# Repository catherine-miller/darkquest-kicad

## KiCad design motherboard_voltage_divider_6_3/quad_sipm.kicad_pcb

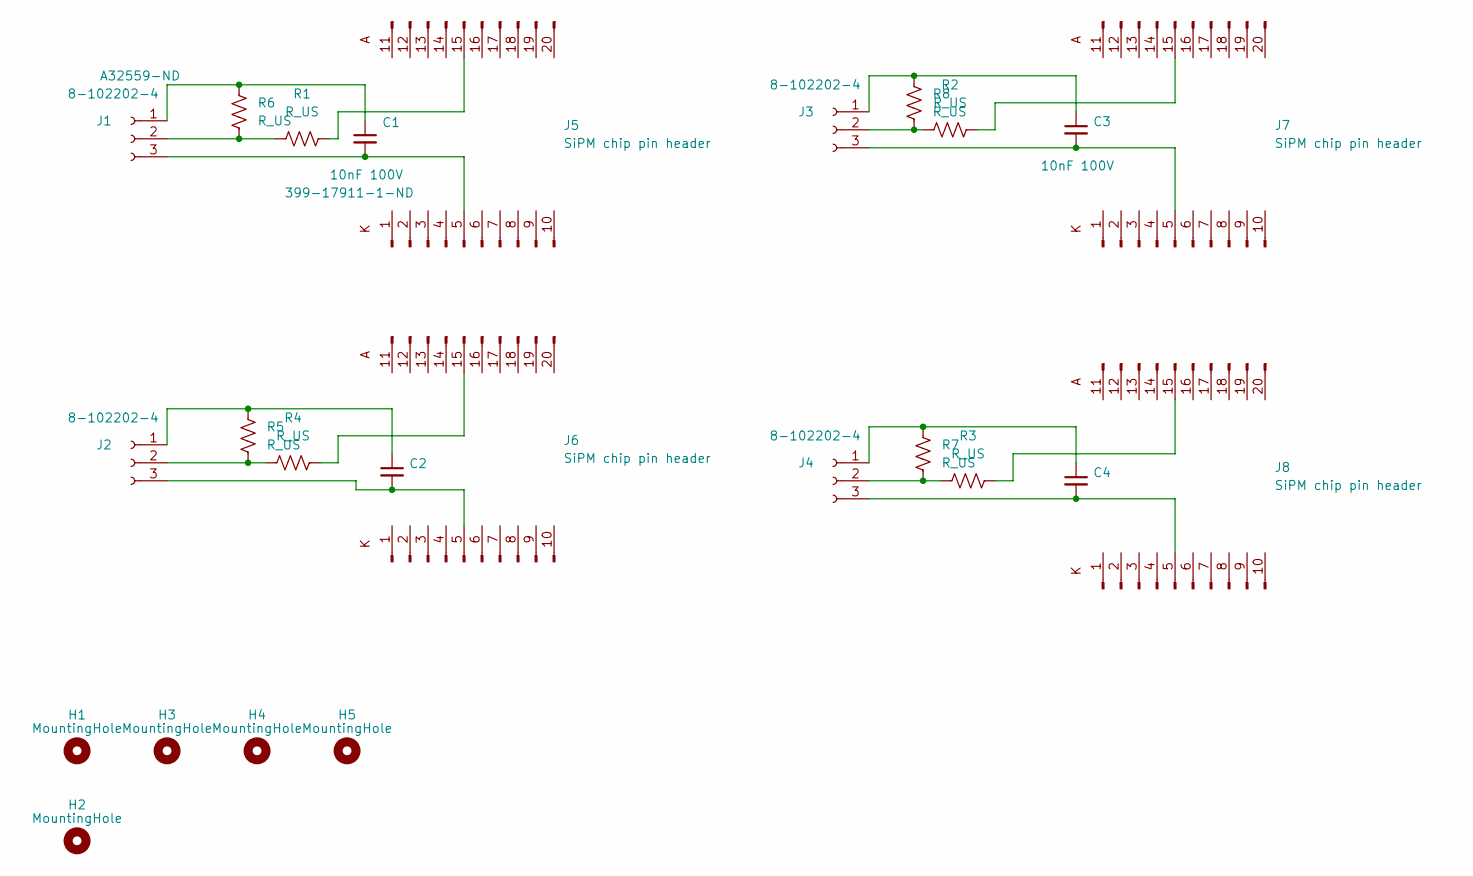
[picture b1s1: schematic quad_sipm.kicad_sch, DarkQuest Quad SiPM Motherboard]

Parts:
C1: 10nF 100V; 1206_VIS-L; DigiKey 399-17911-1-ND
C2, C3, C4: 10nF 100V; C_1206_3216Metric_Pad1.33x1.80mm_HandSolder; DigiKey 399-17911-1-ND
H1, H3, H4, H5: MountingHole; MountingHole_6.4_pad
H2: MountingHole; MountingHole_8.4mm_M8_Pad
J1, J2, J3, J4: 8-102202-4; PinHeader_1x03_P2.54mm_Vertical; DigiKey A32559-ND
J5, J6, J7, J8: SiPM chip pin header; chip_carrier_pin_header
R1, R2, R3, R4: R_US; 1206_VIS-L
R5, R6, R7, R8: R_US; 1206_VIS

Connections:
unnamed: C1.1, J1.1, R6.1
unnamed: J1.2, R1.1, R6.2
unnamed: C1.2, J1.3, J5.5
unnamed: C2.1, J2.1, R5.1
unnamed: J2.2, R4.1, R5.2
unnamed: C2.2, J2.3, J6.5
unnamed: C3.1, J3.1, R8.1
unnamed: J3.2, R2.1, R8.2
unnamed: C3.2, J3.3, J7.5
unnamed: C4.1, J4.1, R7.1
unnamed: J4.2, R3.1, R7.2
unnamed: C4.2, J4.3, J8.5
unnamed: J5.15 (Pin_5), R1.2
unnamed: J6.15 (Pin_5), R4.2
unnamed: J7.15 (Pin_5), R2.2
unnamed: J8.15 (Pin_5), R3.2

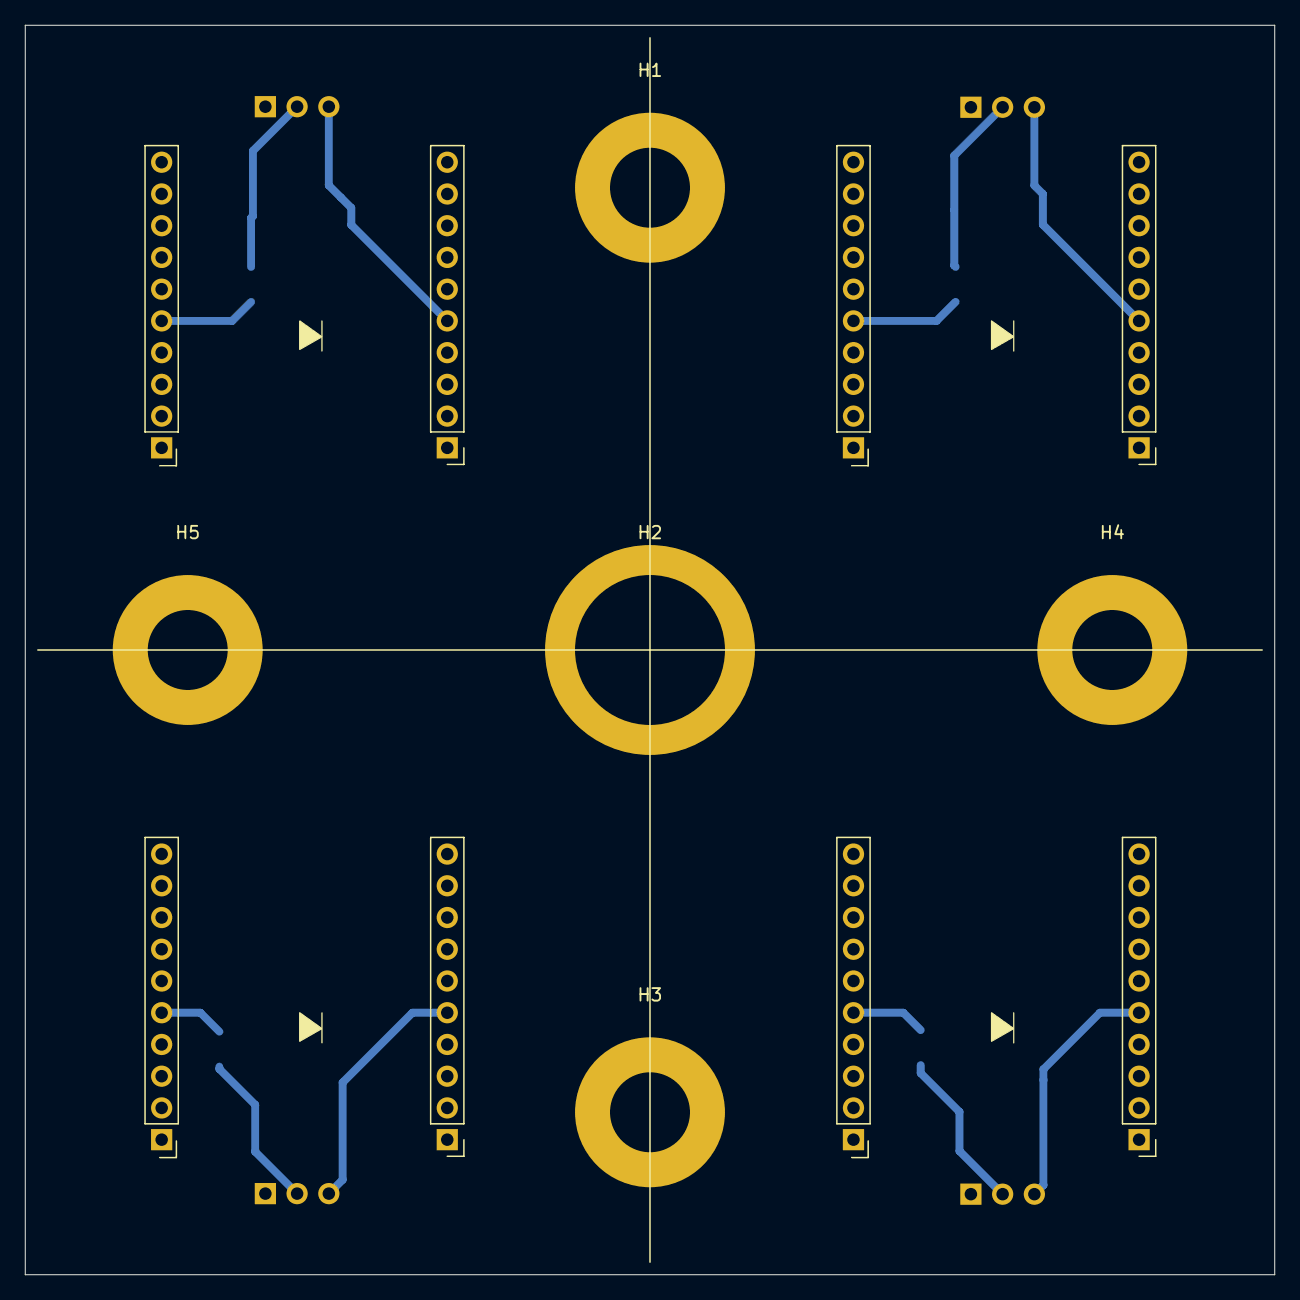
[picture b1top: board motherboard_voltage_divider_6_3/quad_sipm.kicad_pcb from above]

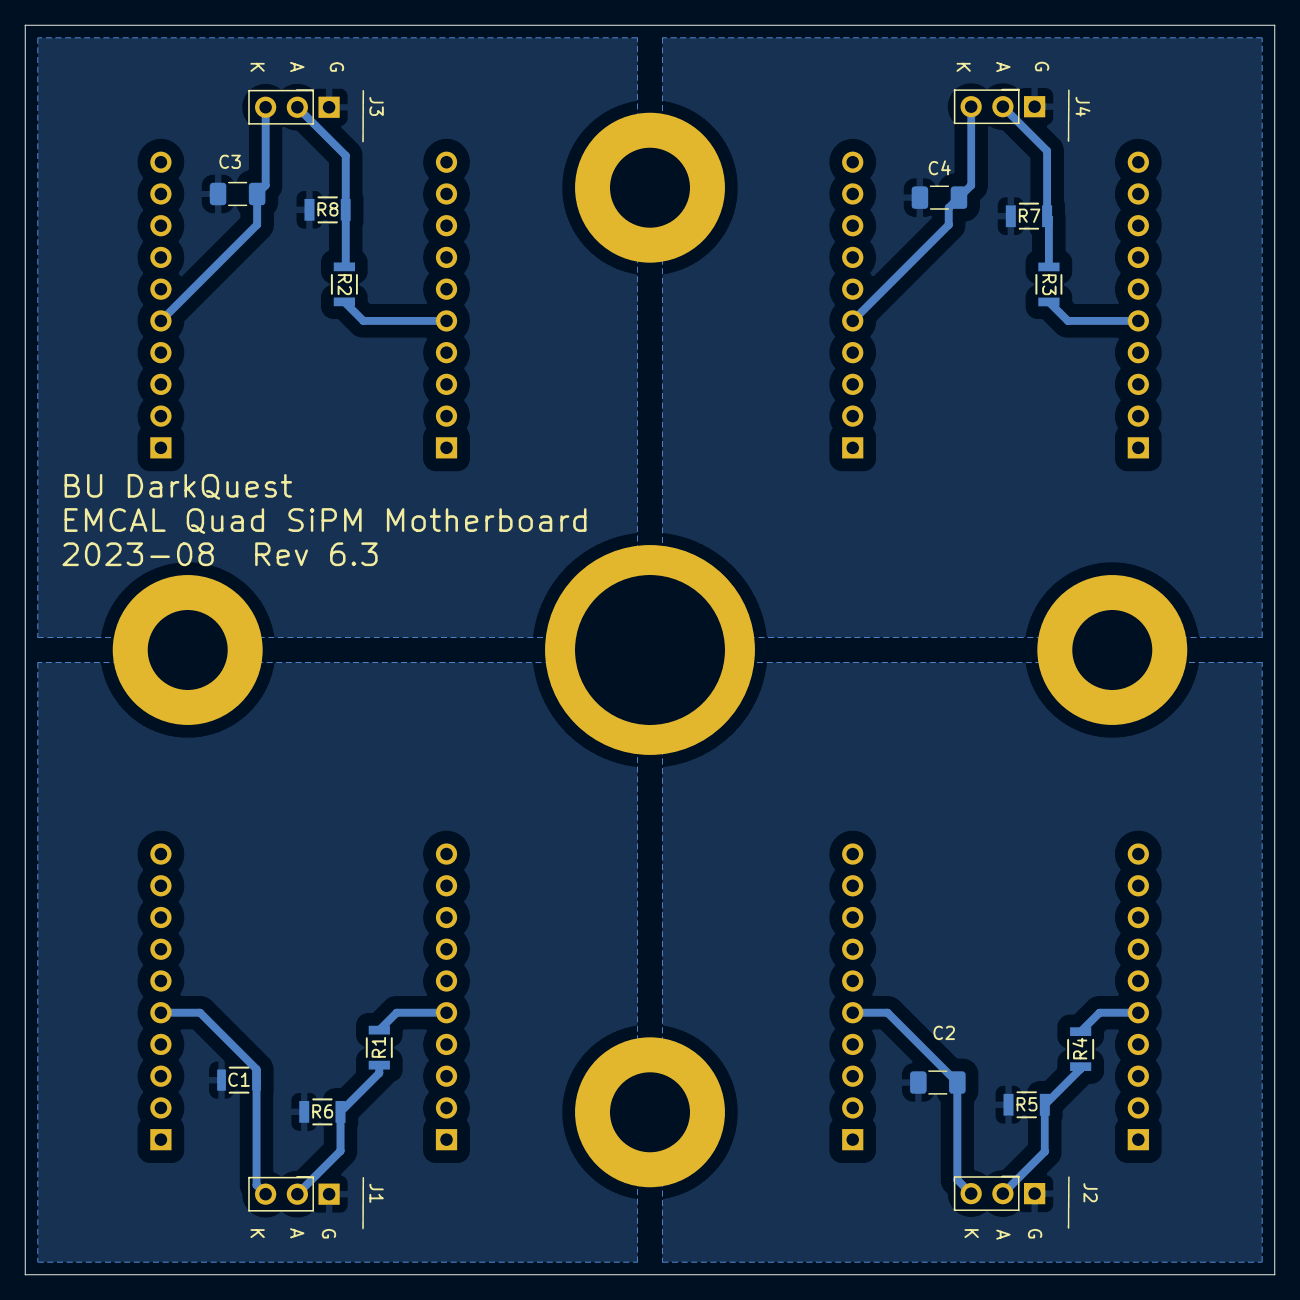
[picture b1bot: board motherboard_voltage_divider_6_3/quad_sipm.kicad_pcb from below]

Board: 2 copper layers, 100.0 x 100.0 mm, 25 parts (16 on the bottom side), 16 nets.

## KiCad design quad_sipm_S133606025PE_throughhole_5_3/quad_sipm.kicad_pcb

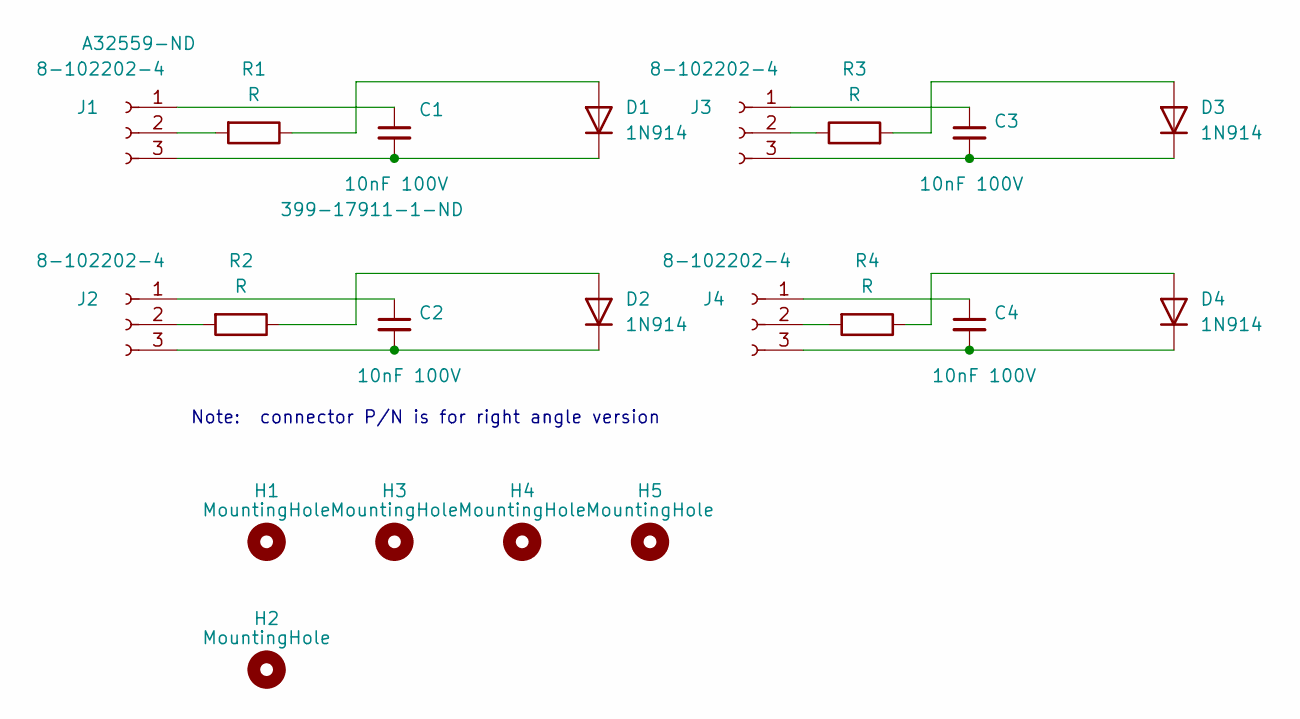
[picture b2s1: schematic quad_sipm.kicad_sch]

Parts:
C1, C2, C3, C4: 10nF 100V; C_1206_3216Metric_Pad1.33x1.80mm_HandSolder; DigiKey 399-17911-1-ND
D1, D2, D3, D4: 1N914; S13360-6025PE_throughhole
H1, H3, H4, H5: MountingHole; MountingHole_6.4_pad
H2: MountingHole; MountingHole_8.4mm_M8_Pad
J1, J2, J3, J4: 8-102202-4; PinHeader_1x03_P2.54mm_Vertical; DigiKey A32559-ND
R1, R2, R3, R4: R; 1206_VIS-L

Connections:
unnamed: D1.2 (A), R1.1
unnamed: C1.2, D1.1 (K), J1.3
unnamed: D2.2 (A), R2.1
unnamed: C2.2, D2.1 (K), J2.3
unnamed: D3.2 (A), R3.2
unnamed: C3.2, D3.1 (K), J3.3
unnamed: D4.2 (A), R4.1
unnamed: C4.2, D4.1 (K), J4.3
unnamed: C1.1, J1.1
unnamed: J1.2, R1.2
unnamed: C2.1, J2.1
unnamed: J2.2, R2.2
unnamed: C3.1, J3.1
unnamed: J3.2, R3.1
unnamed: C4.1, J4.1
unnamed: J4.2, R4.2

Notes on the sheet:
Note: connector P/N is for right angle version

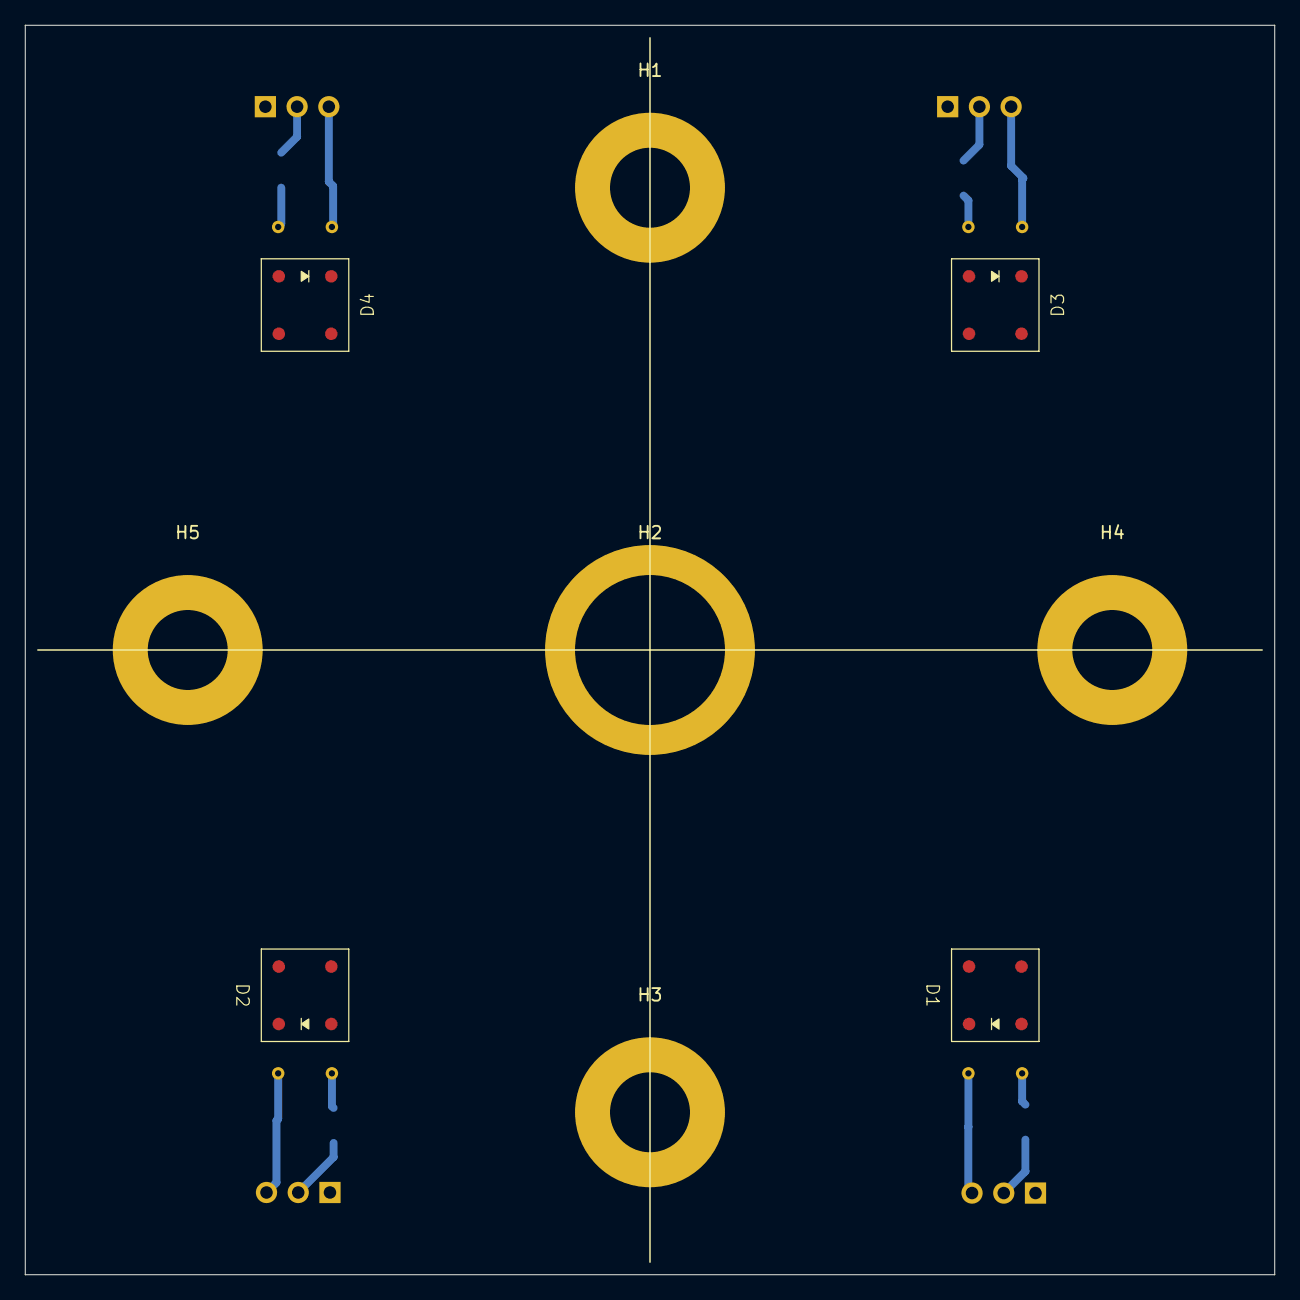
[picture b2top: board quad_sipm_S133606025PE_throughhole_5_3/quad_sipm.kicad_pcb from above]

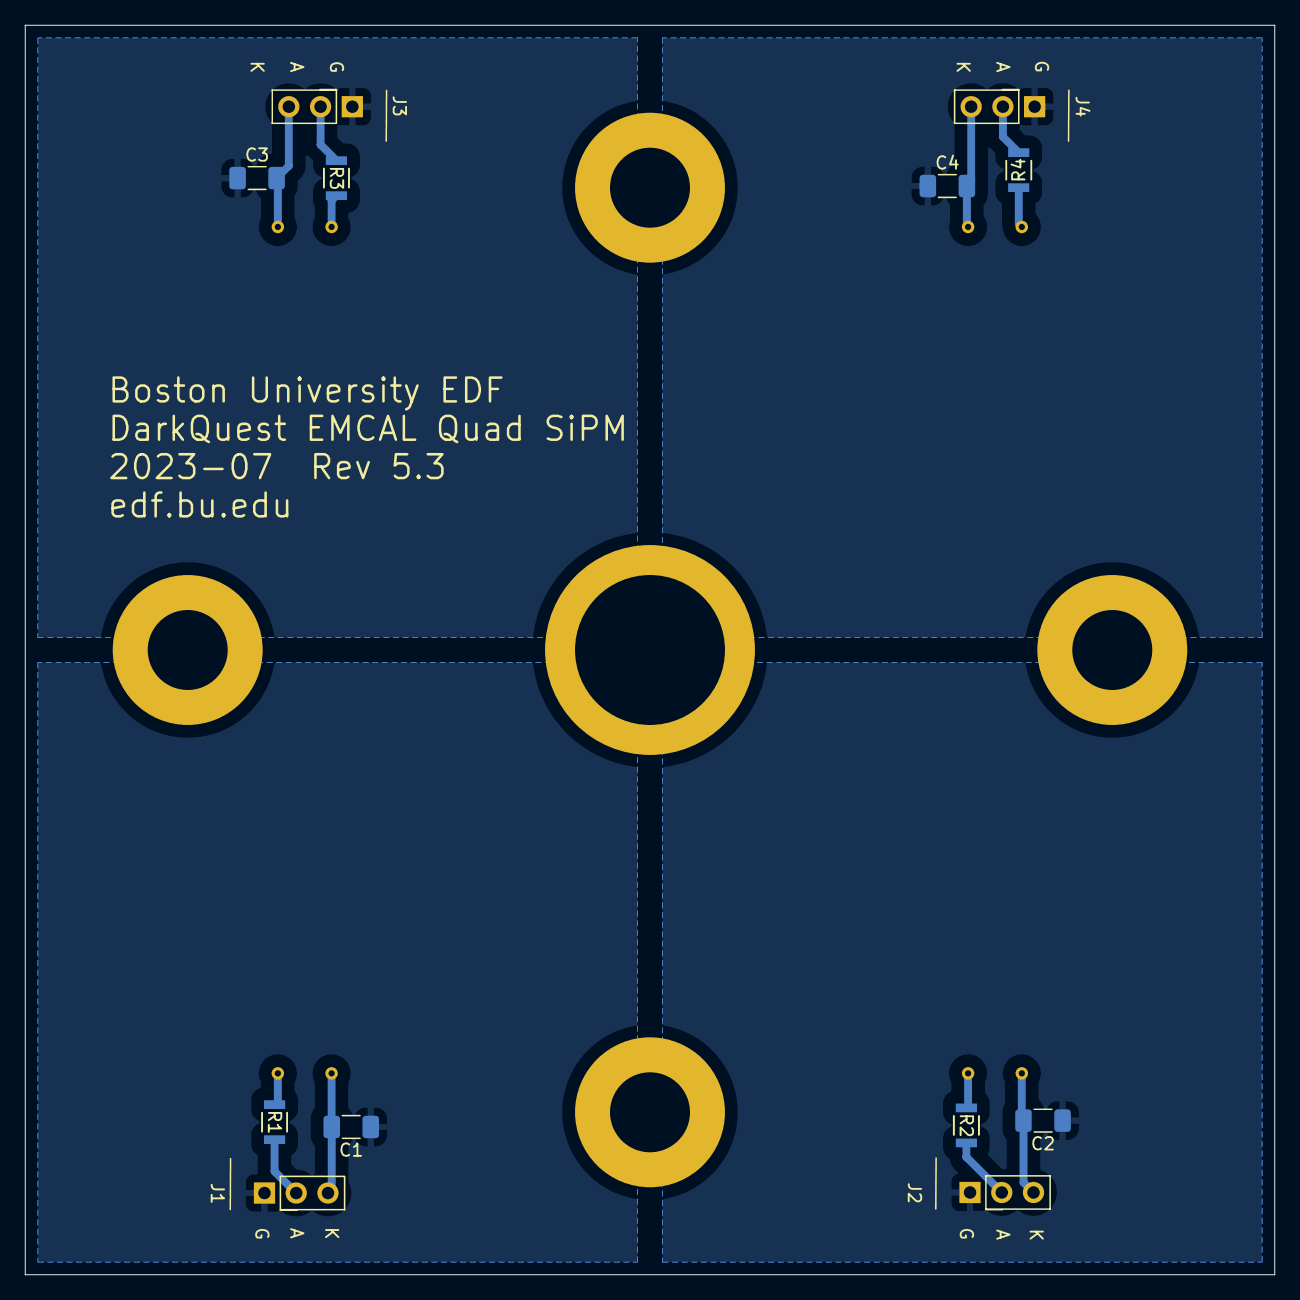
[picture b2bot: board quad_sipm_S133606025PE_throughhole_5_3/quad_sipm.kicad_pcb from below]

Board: 2 copper layers, 100.0 x 100.0 mm, 21 parts (12 on the bottom side), 16 nets.

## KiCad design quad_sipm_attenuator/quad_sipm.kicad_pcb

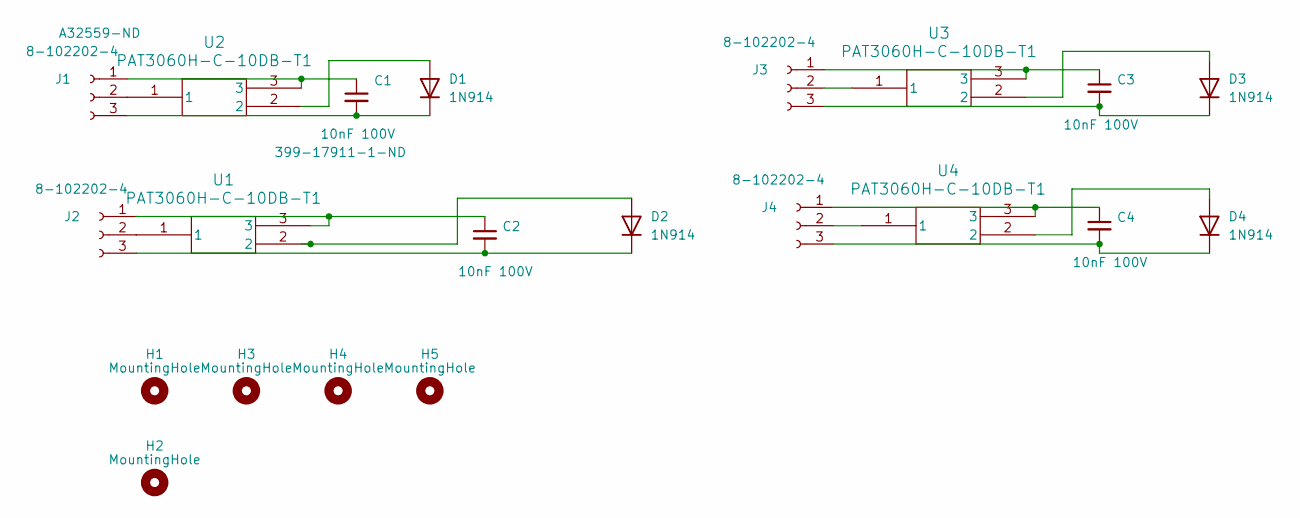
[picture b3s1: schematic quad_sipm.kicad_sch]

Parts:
C1, C2, C3, C4: 10nF 100V; C_1206_3216Metric_Pad1.33x1.80mm_HandSolder; DigiKey 399-17911-1-ND
D1, D2, D3, D4: 1N914; S13360-6025CS
H1, H3, H4, H5: MountingHole; MountingHole_6.4_pad
H2: MountingHole; MountingHole_8.4mm_M8_Pad
J1, J2, J3, J4: 8-102202-4; PinHeader_1x03_P2.54mm_Vertical; DigiKey A32559-ND
U1, U2, U3, U4: PAT3060H-C-10DB-T1; PAT3060H_SUS

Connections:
unnamed: D1.2 (A), U2.2
unnamed: C1.2, D1.1 (K), J1.3
unnamed: D2.2 (A), U1.2
unnamed: C2.2, D2.1 (K), J2.3
unnamed: D3.2 (A), U3.2
unnamed: C3.2, D3.1 (K), J3.3
unnamed: D4.2 (A), U4.2
unnamed: C4.2, D4.1 (K), J4.3
unnamed: C1.1, J1.1, U2.3
unnamed: J1.2, U2.1
unnamed: C2.1, J2.1, U1.3
unnamed: J2.2, U1.1
unnamed: C3.1, J3.1, U3.3
unnamed: J3.2, U3.1
unnamed: C4.1, J4.1, U4.3
unnamed: J4.2, U4.1

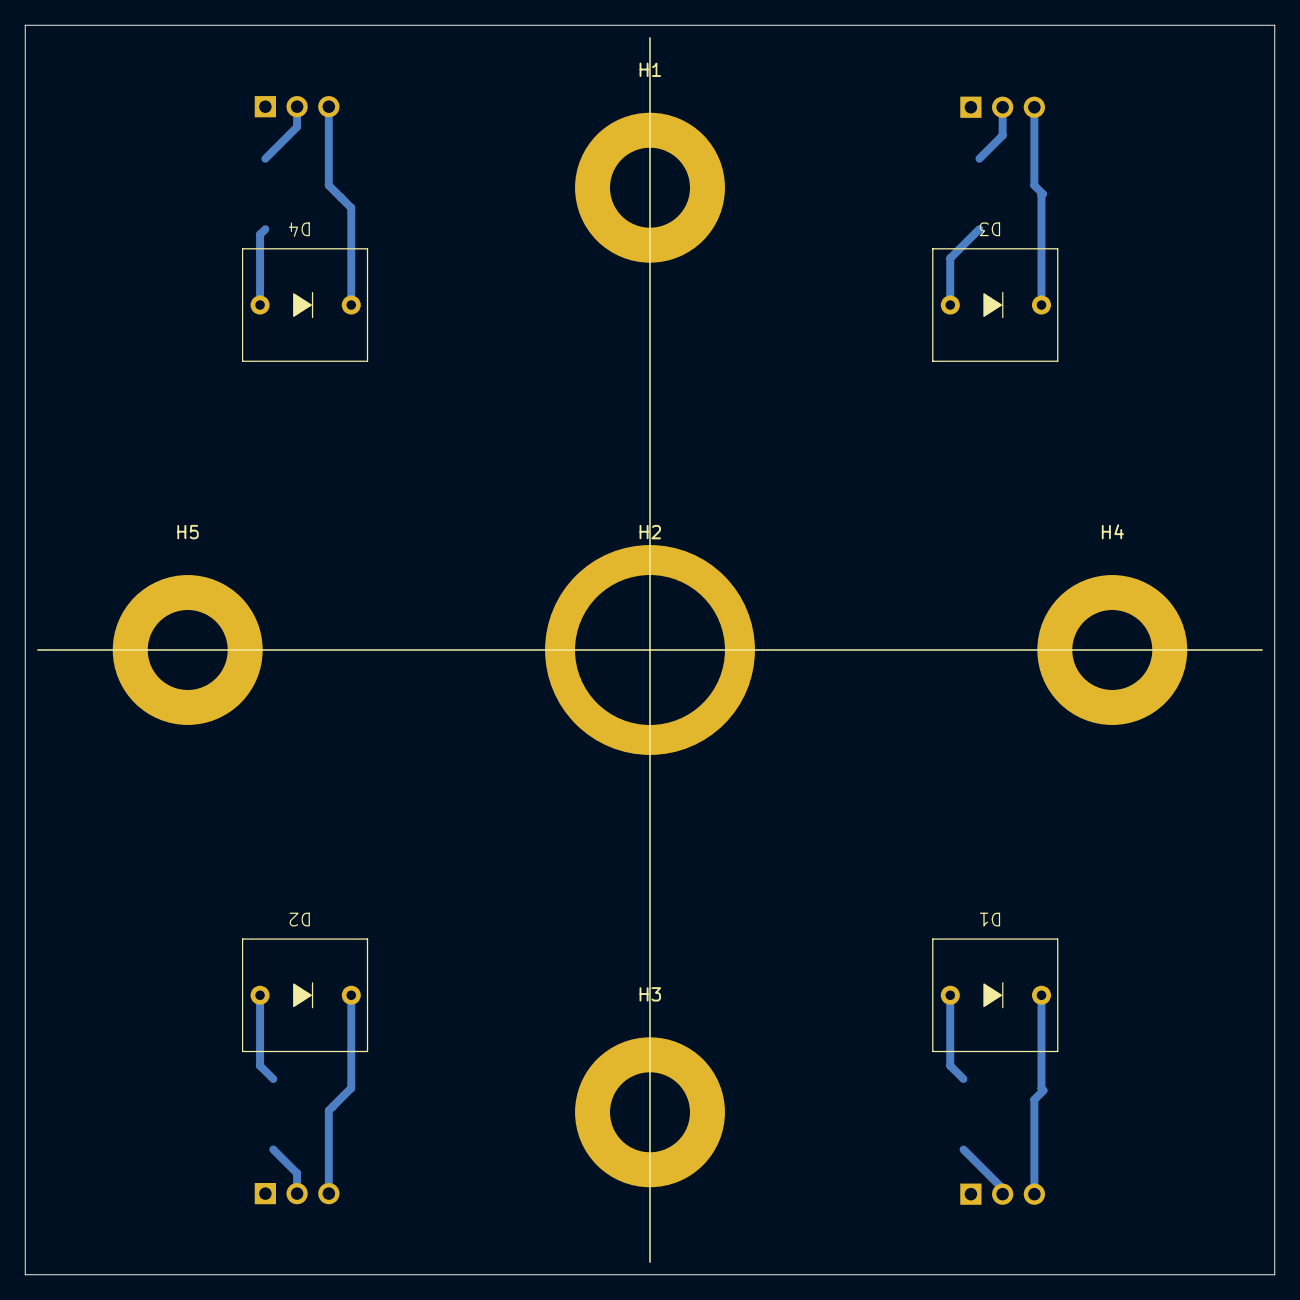
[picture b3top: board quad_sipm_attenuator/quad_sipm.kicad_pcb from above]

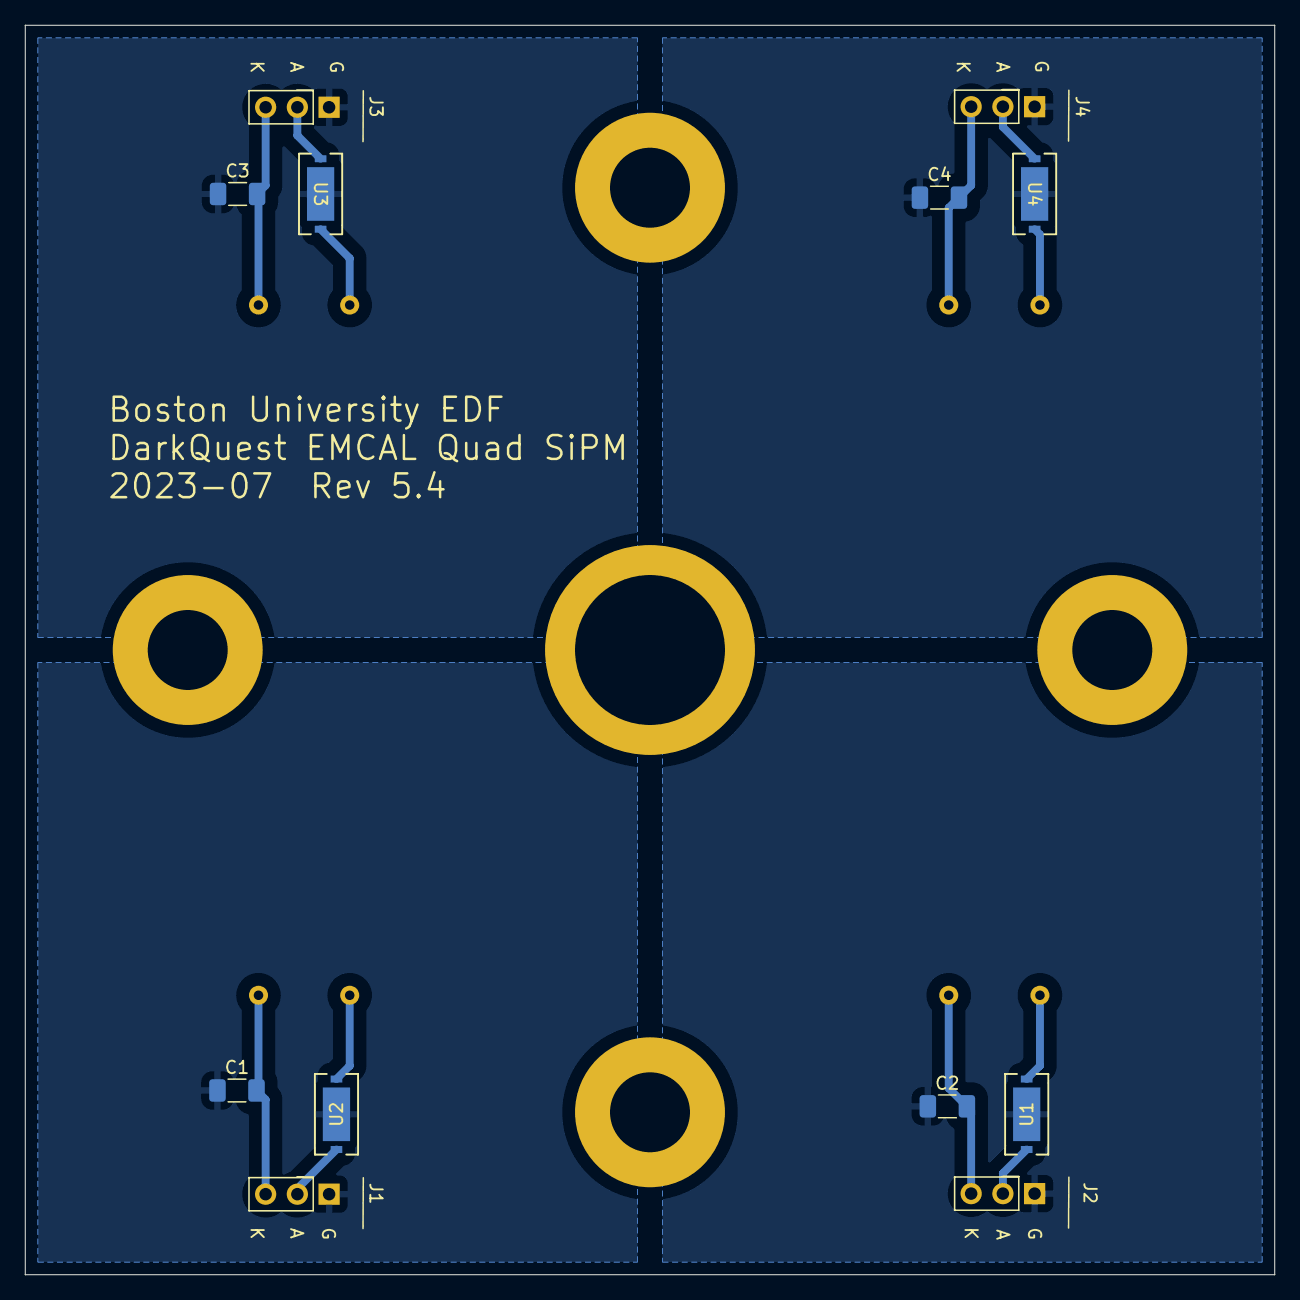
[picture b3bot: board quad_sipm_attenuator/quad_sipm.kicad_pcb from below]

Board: 2 copper layers, 100.0 x 100.0 mm, 21 parts (12 on the bottom side), 16 nets.

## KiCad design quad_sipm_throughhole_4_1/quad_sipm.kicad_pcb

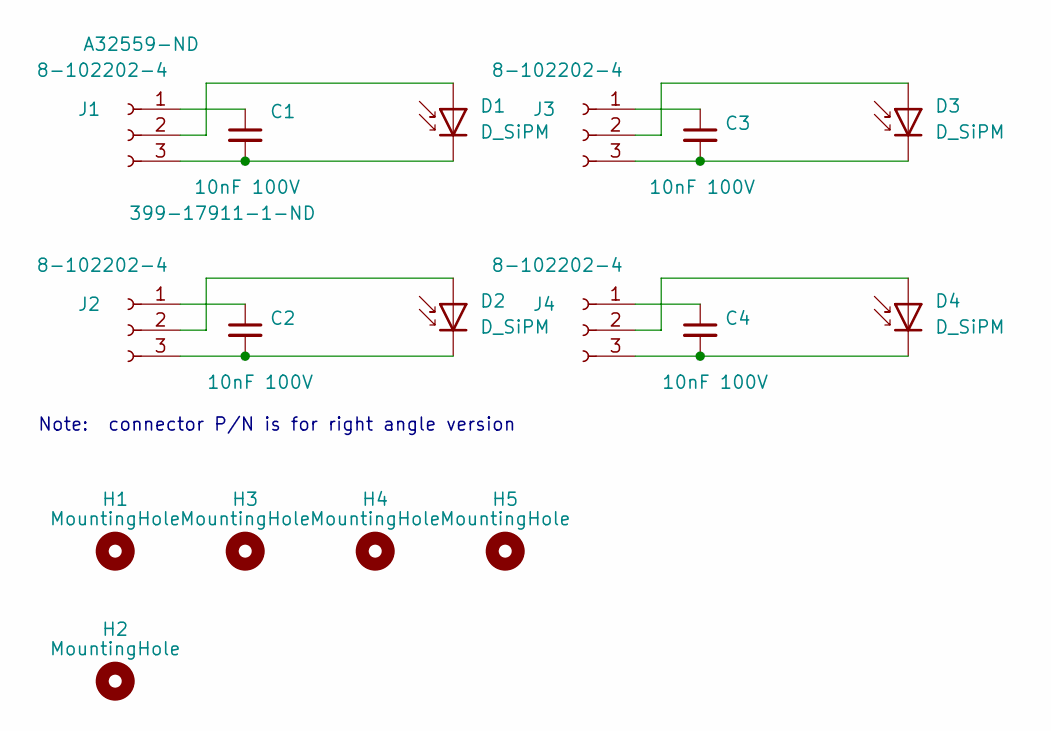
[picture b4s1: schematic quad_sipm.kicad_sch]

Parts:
C1, C2, C3, C4: 10nF 100V; C_1206_3216Metric_Pad1.33x1.80mm_HandSolder; DigiKey 399-17911-1-ND
D1, D2, D3, D4: D_SiPM; SiPM_throughhole
H1, H3, H4, H5: MountingHole; MountingHole_6.4_pad
H2: MountingHole; MountingHole_8.4mm_M8_Pad
J1, J2, J3, J4: 8-102202-4; PinHeader_1x03_P2.54mm_Vertical; DigiKey A32559-ND

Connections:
unnamed: D1.1 (A), J1.2
unnamed: C1.2, D1.2 (K), J1.3
unnamed: D2.1 (A), J2.2
unnamed: C2.2, D2.2 (K), J2.3
unnamed: D3.1 (A), J3.2
unnamed: C3.2, D3.2 (K), J3.3
unnamed: D4.1 (A), J4.2
unnamed: C4.2, D4.2 (K), J4.3
unnamed: C1.1, J1.1
unnamed: C2.1, J2.1
unnamed: C3.1, J3.1
unnamed: C4.1, J4.1

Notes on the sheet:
Note: connector P/N is for right angle version

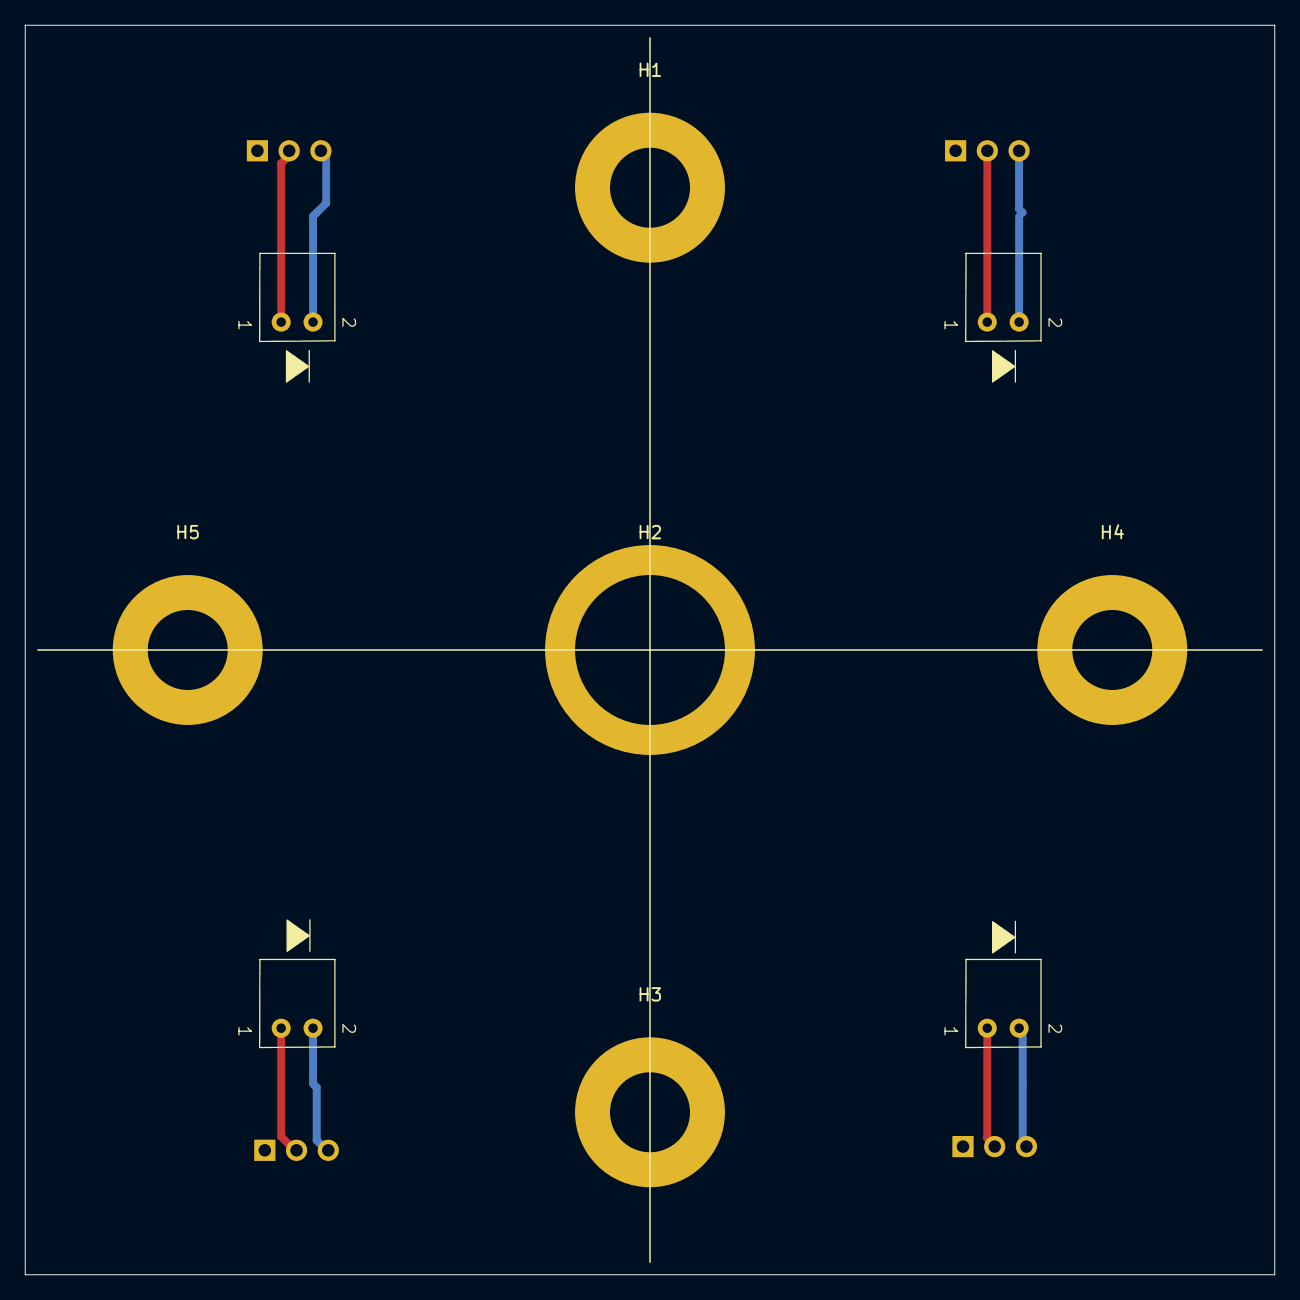
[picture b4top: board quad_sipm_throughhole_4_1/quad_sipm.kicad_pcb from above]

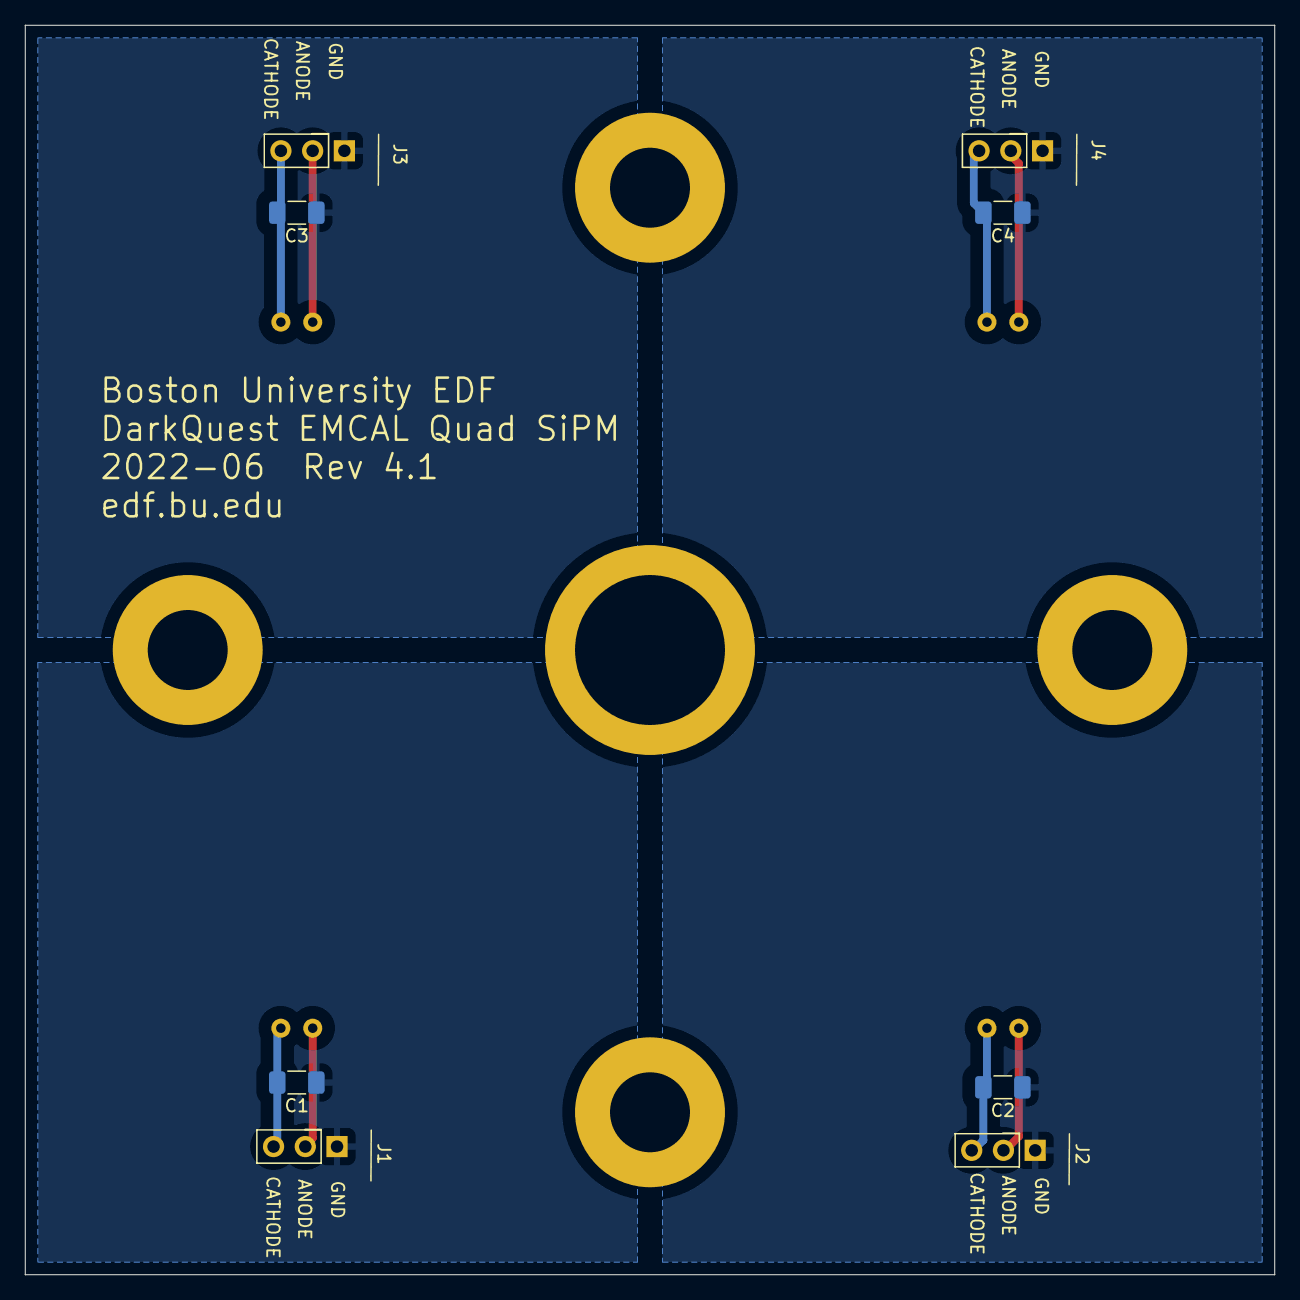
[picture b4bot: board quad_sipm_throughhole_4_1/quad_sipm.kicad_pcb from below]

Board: 2 copper layers, 100.0 x 100.0 mm, 17 parts (8 on the bottom side), 12 nets.
